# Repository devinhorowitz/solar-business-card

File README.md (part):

# SOLAR-GLOW · DRH

A business card that runs on light. An AVR microcontroller breathes four amber LEDs
*through* the board — a monogram cut into the front copper that glows when the rear LEDs
backlight it through the bare fiberglass — while a pair of indoor solar cells trickle-charge
a supercapacitor bank that holds the charge.

<sub>The assembled card — Ti back-shell, resin diffuser brace, 0.60 mm PCB and eight M2 brass screws.
Not an artist's impression: every surface is the committed STEP-derived STL, the outline and the
eight mount positions come straight out of the `.kicad_pcb`, the Z stack is the one
`enclosure/fit_rules.py` enforces, and the show face is the **raytraced board itself** — the
monogram window, the ENIG, the contactless mark and the contact line are the real artwork, not a stand-in.
Re-route the front and this picture follows. Stills, the exploded and reverse views, and the full
respin are in [`enclosure/README.md`](enclosure/README.md).</sub>

> **Status: v4.0 (managed-solar redesign) in progress** -- working files are `v4_0`, currently the v3.0
> baseline being reworked to the AEM10300 active-harvest architecture (see the design-notes v4 addendum +
> `v4-aem10300-prewiring.md`). **v3.0 -- fully routed, audit-clean, not yet fabbed -- is frozen as the final
> unmanaged-solar revision.**
> Two-layer, 0.6 mm FR4, bound for PCBWay; the 4-layer **v2.3** is the fallback design, kept in git history (not the working tree).
> The one thing standing between here and a build is the **energy budget** — harvest vs. draw under
> real indoor light has never been measured. See *“The open question.”*

### Current revision — the one canonical summary

| What | Current | Notes / fallback |
|---|---|---|
| **PCB** | **v4.0 - 2-layer** (F / B) | GND = full-board B.Cu pour; VS = routed B mesh. **v2.3 (4-layer: F / In1 GND / In2 VS / B) is the fallback design, in git history.** v2.1 was 6-layer (history). |
| Board | 50.80 × 88.90 mm, r3.0 corners, **0.60 mm** FR4, ENIG, matte-black mask | 0.6 mm — committed in the board stackup (frees the shell floor to 1.0 mm) |
| Mounting holes | **8× M2, GND** -- 4 corner (MH1-4) at **(2.87, 2.87) / (47.93, 2.87) / (2.87, 86.03) / (47.93, 86.03)** (pitch **45.06 × 83.16 mm**) + 4 panel-corner (MP1-4) at **(2.87, 28.63) / (47.93, 28.63) / (2.87, 60.27) / (47.93, 60.27)** | corners concentric with the r3.0 fillets; MP1-4 at the E/W mid-edges for the shell clamp |
| **Enclosure** | **Ti back-shell** - 1.00 floor, 1.80 cavity, overall **3.55 mm**; center support via the single-piece resin diffuser brace. **Respun 2026-07-29 against the real board** — the brace had 593 mm³ of resin inside three supercaps and the shell lip sat on 4.17 mm² of live pad; both geometries are now computed from the board and gated by `check_consistency` **[8]**. | 8-hole pattern (4 corner + 4 panel-corner); see [`enclosure/README.md`](enclosure/README.md) |
| BOM | **generated from the design** — there is no hand-authored master; most passives 0402 with the precision/bulk set on **0603** (C4/C13/C25/C22/C23/R5/R6/R15/R16) and **0805** (C26/C27); **SJ1 removed outright 2026-07-30** (lineage row only); Q2 + R18 added by the cold-start-deadlock fix | line items come from `scripts/bom_split.py` (schematic + the board's own `exclude_from_bom`/`dnp` flags); the buy documents are written into `Generated/fabdocs/` every CI run; live availability + pricing in `BOM/README.md` (`python3 BOM/check_stock.py`). Both `*-BOM.xlsx` masters were culled 2026-08-02 and live in git history |
| Firmware | AVR64EA28 C, register-verified **and compile-verified in CI**; not yet on hardware | LED pin map re-mapped in v3.0 (see `firmware/README.md`) |

*How thin 3.55 mm is, in things a hand already knows — thinner than three stacked pennies, almost exactly a ten-card stack of standard business cards, 41% of an iPhone 17 Pro. True relative scale; the card's number is measured from the committed back-shell STL by `scripts/ref_figures.py`, so the figure follows the artifact.*

### Where the truth lives — how these docs stay from drifting

Each fact has exactly one home; everything else points at it rather than restating it.

| Domain | Source of truth |
|---|---|
| Board copper / geometry / holes | `PCB/solar-glow-drh-v4_0.kicad_pcb` + `.kicad_sch` |
| Back-shell medallion (ring text, monogram, serial №) | `enclosure/medallion.py` — the shell generator and its drawing both import it; bump `SERIAL` there and CI regenerates the STEP/STL/drawing (a kibot trigger since 2026-07-31) |
| Fabrication panel (PCBWay) | `scripts/panelize.py` — derived from the board on every CI run into `Generated/panel/`; never hand-maintained |
| README renders | `scripts/render.py` — raytraced from the board/panel on every CI run into `Generated/docs/`; add a target there rather than committing a hand-made image |
| Enclosure **fit rules** | `enclosure/fit_rules.py` — one home for the brace footprint, the lip bands and the boss scallops; both generators import it and check [8] asserts it. That proves the RULES; whether the emitted solids carry them is `scripts/assembly_drc.py`, which slices the STLs (2026-11-12 — a rule one generator never applied passed check [8] for three months) |
| Enclosure part positions | `enclosure/board_parts.py` — true body ∪ pads, read from the committed `.kicad_pcb` |
| Enclosure geometry | `enclosure/solar-glow-drh-v4_0-backshell-0p6b-brace-cad.py` (prints the Z-stack; regenerates the STEP) |
| Assembly views | `enclosure/assembly_render.py` — regenerated from the STLs + the board; not hand-made |
| Firmware pin map + knobs | `firmware/board.h` (+ `firmware/README.md`; both match the schematic) |
| BOM | **the design itself** — `scripts/bom_split.py` derives every line from the schematic plus the board's `exclude_from_bom`/`dnp` flags, and writes the two buy documents into `Generated/fabdocs/` on each CI run. `BOM/README.md` is **derived too**: a live stock/lifecycle/price table regenerated by `BOM/check_stock.py` (needs distributor API keys, so manual-apply like the mask art). _(There is no spreadsheet master; both `*-BOM.xlsx` files were culled 2026-08-02 — git history only.)_ |
| Design *reasoning* / lineage | `solar-glow-drh-design-notes.md` |
| Open work / cross-domain to-dos | `TODO.md` (an index of what's left; each item points back at the files above) |

When a number here disagrees with a source-of-truth file, the source file wins and this table is the
thing to correct. The `solar-glow-drh-v2-*` docs are v2-era history (banner-marked at the top of
each); read them for lineage, not for current values.

---

## What it is

A business-card-sized PCB — **50.8 × 88.9 mm, 0.6 mm FR4, ENIG, rounded corners** — that:

- **Harvests** indoor light with **two** ANYSOLAR solar cells merged into a single solar node (SRC) that feeds the AEM10300 harvester (U8),
  which runs the MPPT and handles reverse-blocking so neither panel back-feeds the
  other - the v3 per-panel blocking diodes are removed.
- **Stores** energy in **four** series-parallel supercapacitors -- a **hybrid tank** (two larger
  SS17 cells + two WS17), **1.40 F at 5.5 V** — two EQUAL 2.8 F stages (SC1∥SC2 above MID, SC3∥SC4
  below), **≈ 21 J nameplate but 15.1 J stored and 9.8 J spendable** once the AEM's strapped 4.65 V
  `VOVCH` ceiling and the 2.75 V glow floor are applied — with the AEM10300 harvester (U8) balancing
  the series midpoint (MID) against leakage mismatch between those two identical stages; the safe 3.3 V VS rail
  is set by the U9 TPS7A0233 LDO, not a shunt clamp.
- **Glows** by back-lighting a **“DRH” monogram** that’s cut into the front copper: a gold
  ENIG field with the three letters opened to bare FR4. Four reverse-mounted amber LEDs on the
  back fire up through the translucent substrate, so the letters themselves light up — and PWM
  on the LED drives makes them breathe.
- **Wakes** to a **tap.** A 3-axis accelerometer feels you pick the card up (or the enclosure
  being tapped) and interrupts the MCU out of sleep — no button, no moving parts.

The front face stays naked — solar cells and the glowing monogram exposed — and the dense work
all lives on the back, ready for an optional machined-metal back-shell.

> **A note on lineage:** earlier revisions (REV J and before) were *generated from Python* —
> geometry and Gerbers emitted by script, no layout tool in the loop. **v2.1 is a full KiCad
> design** (schematic + board), continued through v4.0. The old generators are kept only as
> history; the KiCad files are the source of truth.

---

## How it works

| Block | Part | Notes |
|---|---|---|
| MCU | **AVR64EA28** (28-VQFN) | TCA0 hardware PWM, I²C to the accel, charge/sleep logic; 2026-07 family swap from the AVR64DD28 (12-bit diff ADC + PGA; no MVIO on the EA, so the DD-era SJ1 strap was deleted outright, 2026-07-30) |
| Solar | **2× ANYSOLAR SM141K06TF** | monocrystalline indoor cells (Voc 4.15 V), in parallel — two panels ≈ 2× the harvest |
| Harvest PMIC | **e-peas AEM10300** (U8, QFN-28 4×4) | MPPT buck-boost that merges both panels at SRC and charges the supercap tank (STO) - replaces the v3 per-panel blocking diodes |
| Storage | **2× SCHURTER 3-153-440** (SS17, 1.8 F) + **2× 3-153-438** (WS17, 1.0 F) | hybrid tank, 2.75 V/cell, wired 2S2P as **two EQUAL 2.8 F stages** (SC1∥SC2 `STO`→`MID`, SC3∥SC4 `MID`→`GND`) → **1.40 F @ 5.5 V**; ≈ 21 J nameplate, **15.1 J stored** at the AEM's strapped 4.65 V ceiling, **9.8 J spendable** above the 2.75 V glow floor. AEM holds MID against *leakage* mismatch between the two identical stages — not a capacitance imbalance; there isn't one |
| Midpoint balance | **AEM10300 (U8) BAL** | the harvester balances the 2S supercap midpoint (MID net) - replaces the v3 ALD910025 dual SAB MOSFET |
| Rail regulator | **TI TPS7A0233PDQNR** (U9, X2SON-4 since 2026-08-05) | nanopower LDO (~25 nA Iq) regulates STO down to the fixed **3.3 V VS rail** the MCU + accel run on - replaces the v3 TLV3011 + PNP shunt clamp |
| LEDs | **4× ams OSRAM LA P47F** (amber) | reverse-mount; glow through the FR4 window, **150 Ω** ballast each |
| LED master switch | **SW2** (solder-bridge) | OFF / ON — bridged feeds `ANODE` straight from `STO`, open is a true hardware off _(the TINY dim position and its R12 shared ballast were deleted 2026-08-05; PWM duty owns dimming)_ |
| Motion | **ADI ADXL367** | 3-axis accel; tap / double-tap wakes the MCU via interrupts; 0.89 µA (swapped from LIS2DH12 on backorder) |
| Light sense | **R5 / R6 divider → PD2** | SRC ÷ 2 off the *merged solar input* (not the rail) - tracks light directly; doubles as wake-on-light |
| NFC | **NXP NT3H2211** (NTAG I²C plus 2K) | present from v3.0 - a contact **vCard** a phone taps to save; field-detect (FD, PA6) also wakes the glow - I²C `0x55`, shares the accel's bus; VCC **power-gated by `U6`** (`NFC_EN`/PA7, off by default); the **U7 MB85RC512TY FRAM** (I²C 0x50, C28) rides always-on VS parked in its 0.2 µA I²C Sleep mode (the 2026-07-23 back-power fix - see design notes) |

**Breakouts and features:** a **TC2030** Tag-Connect pad (`TC1`) for hands-free UPDI
programming, a backup UPDI header (`J1`), a **5-pad bench strip** on the back east edge
(`TP1` SRC + `JP1` GND/STO/SCL/SDA - bare SMD probe pads for bench power injection and an I²C
tap; pinout in `solar-glow-drh-v2-hardware.md`), and **eight grounded M2 mounting holes** (four corners + four panel-corner at the E/W mid-edges). (The `SB1–4`
bridges — per-LED **force-on**, not "disable" as this line long said — were deleted with TINY mode on 2026-08-05. The DD-era
VDDIO2 tie jumper `SJ1` is gone — DNP'd at the AVR-EA swap, deleted from the schematic and board outright on 2026-07-30. The v2-era
`JP1`/`JP2` 2.54 mm breakout headers are gone; the `JP1` name is reused for the strip.)

Full part numbers, pricing, and per-part datasheet links are in
**[`BOM/README.md`](BOM/README.md)** - the live availability table (generated; there is no spreadsheet
master, both `*-BOM.xlsx` files were culled 2026-08-02 into git history): every orderable line carries a
live-verified distributor P/N, stock and price, re-checked by `BOM/check_stock.py` rather than typed. **U6 is moving to
TPS22916CYFPR** (DSBGA-4 YFP, 0.5 mm max — the 2026-08-06 ultrathin swap; schematic done, board sync pending — see
`PCB/README.md`'s BOM table. It succeeds the TPS22919 SC-70 that landed 2026-08-05 — itself the leakage upgrade over
the `TPS22917DBVT` — trading +8 nA typical OFF-state leakage for 0.6 mm of height and a 16× better ON-state IQ,
so every component clears 1.1 mm for the ultrathin-card option) with **R14 (1 M `NFC_EN` pulldown)**; the stale
JP1/JP2 rows are dropped (the `JP1` designator is reused in v3.0 for the bench pad strip - bare pads,
no BOM part). Passives are X7R / AEC-Q200 / precision grade: most on **0402** lands, with the
stability upsizes on 0603 (C22/C23, R5/R6, R15/R16, plus the bulk caps C4/C13/C25) and 0805
(C26/C27, and C9's NFC tank cap — fitted 47 pF, derived not trimmed). SJ1 is culled. Lineage: v2.2 added the NFC parts (U5 / C8 / C9 / R13); the `v2 2` and older
BOM files stay in the repo as history.

---

## The board

- **Two copper layers** on 0.6 mm FR4 (v3.0): **F.Cu** signal/parts and **B.Cu**. **GND is a
  full-board B.Cu pour** (`GND_B` zone) with stitch straps, and **VS is a routed mesh on B** — the
  4→2-layer conversion of v2.3, whose internal GND/VS *planes* moved onto the back copper. The
  4-layer **v2.3** (F · In1 GND · In2 VS · B) is the fallback (recoverable from git history) if the
  back-side trace texture showing faintly on the naked front reads wrong.
- **The glow window is a keepout on every layer.** The monogram cutout and the four LED
  light-paths are voided through both layers so nothing — copper pour, trace, or via —
  shadows the light between the rear LEDs and the front face. The rear soldermask is left
  *open* over the window on purpose: bare ENIG reflects the LEDs’ light forward instead of
  absorbing it.
- **Rail discipline.** The supercap stack can sit near 5.5 V, but the accelerometer tops out at
  3.6 V - so the **U9 TPS7A0233 LDO** regulates the supercap tank (STO) down to the fixed
  **3.3 V VS rail**, directly bounding what the accelerometer sees. Its ~25 nA quiescent
  draw is negligible against the other always-on loads, and it regulates VS itself rather
  than the solar input. (v3's TLV3011 + PNP shunt clamp and the per-panel blocking diodes
  are gone - the AEM10300 now owns the harvest path.)
- **Power planes** carry the supercap charge/discharge currents; the four cells eat the better
  part of the back, so the layout is geometry-bound and the planes earn their layers.

---

## The open question — read this before building a batch

The board is well-verified; the **energy budget is not.** A solar cell’s headline rating is a
full-sun number, and indoor light delivers a small fraction of it, while four breathing LEDs
average several milliamps. The two-panel harvest and the tank — **9.8 J spendable**, not the 21 J
nameplate — are sized to **harvest
slowly and glow in bursts** — but that bet has never been put on a meter.

What changed the math since the early notes: the LED string is fed from the **STO supercap tank** (through the
SW2 anode switch), which the AEM10300 holds at up to **4.65 V** (VOVCH), and the ballasts are **150 Ω** -- so each
LED peaks near **~16 mA** at a full tank ((4.65 V - amber Vf ≈ 2.25 V)/150 Ω, the figure `firmware/README.md`
quotes), sagging toward zero as STO discharges. (VS, the regulated 3.3 V LDO output, powers the MCU and accel,
not the LEDs.) Four on at once is a real load against an indoor harvest measured in fractions of a milliamp.

**First move when boards arrive:** put the cells under your actual target lighting and measure
**harvest current against LED draw** before you populate a full stack. That single number sizes
the duty cycle, the feature set, and whether the always-on accelerometer earns its microamps.

---

## Repository layout

```
solar-business-card/
├── README.md                       # this file (canonical current-revision summary)
├── PCB/                            # KiCad projects
│   ├── solar-glow-drh-v4_0.kicad_pcb   # the board: v4.0 managed-solar rework (AEM10300), 2-layer (source of truth)
│   ├── solar-glow-drh-v4_0.kicad_sch   # schematic: synced to the v4.0 board netlist
│   └── README.md                       # order & build guide
├── BOM/                            # bill of materials (moved from PCB/ 2026-08-01)
│   ├── README.md                       # GENERATED live availability/price table (check_stock.py)
│   ├── check_stock.py                  # live DigiKey/Mouser availability check -> README.md
│   └── README.md                       # DERIVED: stock/lifecycle/price table with red-X dead lines (regenerate, don't edit)
├── solar-glow-drh-design-notes.md  # design rationale, energy model, lineage (incl. the v3.0 chapter) — the one prose file that stays at root, beside this README
├── docs/                           # project notes & records (moved from root 2026-08-01) + the LED sweep tuner
│   ├── solar-glow-drh-v2-hardware.md    # as-built wiring & pin map (v2-era lineage; banner at top)
│   ├── solar-glow-drh-v2-mechanical.md  # board mechanics, keepouts, access (v2-era lineage; banner at top)
│   ├── v4-aem10300-prewiring.md         # the v4 net/pin plan — applied 2026-07-30, kept as the record
│   ├── v4-schematic-sync-checklist.md   # the sch→board sync procedure — DONE, kept as the record
│   ├── harvest-bench-fixture-handoff.md # the energy-budget bench fixture (the #1 open gate's rig)
│   ├── harvest-budget-test-board.md     # the harvest test-board concept
│   ├── eink-display-variant-notes.md    # e-ink variant study (concept, not adopted)
│   ├── firmware-to-pcb-open-items.md    # v3-era cross-team memo (SUPERSEDED; record only)
│   ├── mcp-setup.md                     # sourcing MCP servers setup (DigiKey/Mouser)
│   ├── kicad-happy.md                   # the external second-opinion analyzer: pinned run recipe + the 2026-08-01 baseline triage
│   ├── thomsonlint.md                   # the ontology-guided second reviewer: pinned run recipe + the 2026-08-01 review record
│   └── led-sweep-tuner.html             # interactive LED-constant sandbox (firmware/README links it)
├── firmware/                       # bare-metal C (AVR64EA28); compile-verified, see firmware/README.md
├── bench/                          # pogo-plate bench monitor: Pico firmware + host dashboard (see bench/monitor)
├── datasheets/                     # fitted parts + documented substitutes, named "REF  MPN  $price.pdf"
│                                   #   (survey sheets and replaced-part docs culled 2026-08-01 — git history)
├── enclosure/                      # Ti back-shell + resin brace: CAD / STEP / STL / drawings / assembly views
│                                   #   fit_rules.py + board_parts.py = the geometry both generators derive from
└── (v0-prototype/ and enclosure/engraving-studies/ culled 2026-08-02 — concluded history, kept in git history; the medallion the studies produced ships in enclosure/medallion.py)
```

---

## Building the board

The board is a KiCad project — open it, run DRC, and export the fab set:

1. Open `solar-glow-drh-v4_0.kicad_pro` in **KiCad** (2026 file format).
2. **Run DRC.** It comes back clean apart from the intentional exceptions catalogued in
   `PCB/README.md` and `solar-glow-drh-design-notes.md` (the NFC coil `LA`↔`LB` short, the eight
   GND-tie mounting-hole/gold-frame contacts, the two plating-bus stubs crossing Edge.Cuts at
   x=25.4, the illumination copper inside the glow window, and the benign `lib_footprint_issues`
   plus the **intentional** `BTN` global label on PA5 — the documented future-button pin
   (a deliberate no-fit; recipe in `firmware/README.md`), not a loose end). Fill zones (press **B**) before checking.
3. **Plot Gerbers + drill** from KiCad's own Fabrication Outputs and order from **PCBWay**
   (**2-layer**, 0.6 mm; selective hard gold + plating bus + resin-fill/cap per `PCB/README.md`).

> The supercap land is the one thing to never get wrong. **Both** SCPC cells — the 39 mm
> **SS17** (SC1/SC3) and the 28.5 mm **WS17** (SC2/SC4) — solder to **flat pads under the body**
> (the asymmetric P/N widths are the polarity key), **not** to the folded end tabs, which are
> non-solderable mechanical locators. The footprints here are built to the correct under-body
> land; don't substitute an end-tab land.
>
> Mind the two lengths. Assuming every cell was the 28.5 mm WS17 is exactly what put 593 mm³ of
> brace inside SC1 and SC3 — see [`enclosure/README.md`](enclosure/README.md).

---

## Assembly order (when boards arrive)

1. **Validate the energy budget first** — harvest vs. LED draw under real lighting (above).
2. **Reflow the SMD parts** — the QFN MCU and the LGA accelerometer need hot air / a hotplate;
   the EP and the accel pad reflow to their planes.
3. **Flash firmware** over UPDI — the Tag-Connect pad (`TC1`) is the no-header path; `J1` is the
   backup header. **This step moved ahead of the cells on 2026-07-30**, when TC1 was deliberately
   moved to `F.Cu`: PV1's body covers the pad cluster, so a pogo cable cannot reach it once the
   cell is on. The trade is a good one — the old position was under `SC1`, which is *reflowed*, so
   the window used to close before the board was even finished. See the warning box in
   [`PCB/README.md`](PCB/README.md).
4. **Hand-solder last** — the solar cells (heat-sensitive: ≤ 260 °C / 2 s, no IPA), and set the
   **SW2** bridge: bridged = ON, open = OFF.

---

## Firmware

A first implementation now lives in **`firmware/`** — bare-metal C, **verified at the register
level** against the AVR64EA28 and ADXL367 datasheets and **compile-verified in CI** (warning-free
against the AVR-Ex DFP; not yet run on hardware). Its knobs, wake model, and power notes are in
**`firmware/README.md`** (authoritative); the wiring it targets is **`firmware/board.h`**, which
`check_consistency` **[1]** holds against the schematic netlist pin by pin. (The complete v2-era
pin map in **`solar-glow-drh-v2-hardware.md`** is lineage, not a current source — see the truth
table above.) Final
duty-cycle and feature tuning stay **gated on the energy-budget measurement** below. In short,
the board gives it:

- **LED breathing** — the four LEDs sink into **PA0–PA3 = TCA0 WO0–WO3**, so split-mode PWM
  drives all four as independent 8-bit channels (the 150 Ω ballast sets the peak; PWM sets the
  average, so you trim brightness *below* that ceiling).
- **Tap-to-wake** — the accelerometer’s two interrupts land on **PF1 / PF0**; configure
  tap / double-tap and let it pull the MCU out of sleep.
- **NFC contact tag** — `U5` (NXP NT3H2211, on the board from v3.0) carries a **vCard** a phone reads on a
  tap to save the contact (RF-powered, so it reads with the cap flat), and its **field-detect**
  line wakes the same glow. The tag has no sleep state and would draw **~195 µA** continuously — the
  card's largest idle load — so firmware **power-gates** its VCC through a load switch (`U6`) on
  **NFC_EN (PA7)**, held **off by default** and raised only around an I²C access; the vCard read and
  the FD-wake both run on the phone's field power, so they still work with the tag's VCC off. Shares
  the I²C bus with the accel (`0x55` vs `0x1D`). See `firmware/README.md` → *NFC contact card*.
- **Light sensing** - the divider taps the **merged solar node SRC** (SRC ÷ 2) into **PD2** (AIN2), so it
  reads light directly — ~0 V dark, rising under light; firmware adapts the glow to available
  light and can also read **VDD/10** and the internal temp sensor.
- **Wake-on-light** — the card can also wake when light appears, with no tap. The implemented
  path is an **RTC-timed ADC poll** in deep Power-Down (sample PD2/AIN2 every ~1–2 s, glow on a
  dark→light rise). The tempting *instant* AC0-comparator version was checked against the
  datasheet and found **non-viable on this part** — the AC interrupt doesn't update with the
  peripheral clock stopped, and the AC isn't a Standby/Power-Down wake source, so it would never
  fire. Instant response isn't lost: the accelerometer interrupt wakes from Power-Down, and
  picking the card up to carry it into the light *is* that motion. (Standing current: **≥ ~2.7 µA — a
  2.0 V-referenced lower bound, not a measurement** (the 2026-08-01 pressure test found the NFC tag's
  FD-pin leakage, 1.5 µA typ / 10 µA max, unbudgeted in that sum) — the always-on accelerometer
  (ADXL367, 0.89 µA typ *at 2.0 V*) no longer dominates it, and neither the poll nor the NFC tag do,
  the latter being power-gated off by default — see `firmware/README.md` "Power notes" for the honest
  ledger and the bench item.)
- **Low-power housekeeping** — `VREGCTRL.PMODE = AUTO` for sub-µA power-down; RTC/PIT off the
  internal ULP oscillator (no crystal); an EEPROM “times-activated” counter that survives a
  full supercap drain; and the core **IDLE-sleeps through the breathing glow** while TCA0 keeps
  the PWM running, rather than busy-waiting. (An autonomous CCL + EVSYS light-wake is a possible
  v-next, but isn't what the current firmware does.)

Still open (what the bench measurement unlocks): final breathing-curve and tap-gesture tuning,
charge / brown-out management around the supercap bank, and the duty-cycle adaptation the
harvest number sizes.

---

## Enclosure

A back-only **machined-titanium** shell hugs the populated rear; the front stays naked. A
single-piece **resin diffuser brace** fills the cavity, carries centre support, backs the
monogram window and holds the ferrite over the NFC coil. CAD, STEP, STL, fab notes and
dimensioned drawings are in `enclosure/` — full detail in
[`enclosure/README.md`](enclosure/README.md).

**Respun 2026-07-29 against the real board, because neither part would have assembled.** The
brace's middle band was sized for supercap bays ending at y31.15 / y57.75 — the 28.5 mm WS17
length — while SC1/SC3 are 39 mm SS17 cells, so it put **593 mm³ of solid resin inside three
1.70 mm cans**. The shell's support lip landed on nine B-side parts including **4.17 mm² of
live pad** (`STO`, `STO_LDO`, `VS`, `NFC_EN`) under grounded titanium — fitting it shorted the
storage rail — and five of the eight M2 bosses fouled a part, two on live nets.

Both geometries are now **computed from the board** (`enclosure/fit_rules.py`, reading part
positions from `enclosure/board_parts.py`) rather than hand-placed, and gated by
`check_consistency` **[8]**. Interference is structurally impossible: a part the brace cannot
span is *subtracted* from its footprint rather than pocketed. No board change was required.

The decisions that matter once it's cut: **titanium (Ti-6Al-4V Grade 5)**, **3-axis CNC-milled**
by PCBWay, **bead-blast** finish. The cavity is **cap-limited to 1.80 mm** by the four 1.70 mm
supercaps; the floor is a **true uniform 1.00 mm** (the old 0.05 mm U7 relief pocket was deleted
2026-07-28 — U7 is the 0.90 mm DFN-8, not the 1.75 mm SOIC it was sized for); overall height
**3.55 mm**. **Eight** bosses on the v4 8-hole pattern (four corner, concentric with the r3.0
fillets, plus four panel-corner), each **scalloped** clear of whatever fouls it — a supercap by
that can's own bay clearance, since its body tolerance lands on the edge the boss faces — while
keeping ≥ 80.3 % of its M2 thread annulus. Retention is **eight M2×3 slotted brass screws**, not a press
fit; the head is Ø3.0 and the tip lands **flush** in a Ø3.0 back spotface.

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
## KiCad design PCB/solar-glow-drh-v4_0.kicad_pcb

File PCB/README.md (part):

# SOLAR-GLOW · DRH - PCB (v4.0): Order & Build Guide

<table>
<tr>
<td width="50%"></td>
<td width="50%"></td>
</tr>
<tr>
<td align="center"><b>Front</b> — the card face</td>
<td align="center"><b>Back</b> — the component side</td>
</tr>
</table>

**This is what PCBWay ships**: the 1-up card still attached to its 65.6 × 103.7 mm frame, before
you snap the two tabs. The gold ring inset in the frame is the hard-gold plating bus, mask-opened
so the plating rack has bare copper to clip, with a spur crossing each break tab into the card at
x = 25.4. Both faces are raytraced from the panel CI actually generates — see
`scripts/render.py`, and "The PCBWay panel" below. No components are shown because none are
fitted at this stage; that is the fab's deliverable, not an omission.

## Assembled

<table>
<tr>
<td width="50%"></td>
<td width="50%"></td>
</tr>
<tr>
<td align="center"><b>Back</b> — 53 fitted parts</td>
<td align="center"><b>Front</b> — the two solar cells</td>
</tr>
</table>

The same board with its components on: 52 of the 73 footprints carry a 3D body, which is every part
that actually gets populated (recounted 2026-08-05 after SB1–4 and R12 left with TINY mode; the
2026-08-01 count was "53 of 78"). The other 21 are the drill/mount set (MH1–4, MP1–4, `NPTH_mech`),
the SW2 solder bridge, the bare programming and probe lands (TC1, `TC1/b`, TP1–TP7, JP1),
and **J1**, which is DNP.

> **Read the big grey slabs as ENVELOPES, not as photographs.** The four supercaps, the two solar
> cells, the LEDs, both QFNs, the FRAM, the accelerometer and the NFC tag are **clearance solids**
> generated by `scripts/make_3d_models.py` — each is its part's maximum outline at its **maximum**
> height, because the question they exist to answer is "does the brace clear it?" and a pretty model
> at the wrong height would be worse than useless. They are not appearance references. The chip
> passives and SOT-23s are stock KiCad models and do look roughly like the real parts.
>
> The supercap **locator tabs are deliberately absent** — see `TODO.md`; their real folded geometry
> has never been measured, so the envelope near the two short edges is unverified.
>
> **Every body you see is rendered from this repo, not from a KiCad install.** The nine stock models
> live in `PCB/kicad-3dmodels/` because the image CI renders in carries no 3D library at all — that
> was measured, not assumed (`models: 15/53 resolve ... NO stock 3D library found`), and it is why an
> earlier version of this render was missing every chip passive and both SOT-23s. `render.py` points
> `${KICAD10_3DMODEL_DIR}` at the vendored copy when the host has none, and consistency check [5]
> fails if a new part references a stock model nobody vendored.

---

This folder holds the **board** for SOLAR-GLOW · DRH — the KiCad project, the bill of
materials, and the artwork reference for the SW2 selector. It is the thing you fab and
populate. This README is the procedure: **how to order the bare PCB, how to order the
parts, and how to build the assembly.**

> **One revision lives here.** As of 2026-07-28 that is **v4.0**; the seven `*-v3_0.*` files
> (board, schematic, project, prl, dru, and both BOMs) were removed, the same way v2_1–v2_3 were
> before them. Superseded revisions are kept by git, not by this folder — carrying a second 1.6 MB
> board around only invites someone to open the wrong one. To get one back:
> ```sh
> git log --diff-filter=D -- PCB/solar-glow-drh-v3_0.kicad_pcb   # the commit that removed it
> git show <sha>^:PCB/solar-glow-drh-v3_0.kicad_pcb > /tmp/v3.kicad_pcb
> ```
> **`enclosure/solar-glow-drh-v4_0-backshell-*` is unaffected.** Those files are current and
> fab-ready. _(They carried `v3_0` names until 2026-08-19 — the revision the shell was first cut
> against — and this note used to explain why that was fine. It stopped being fine when the
> DRAWING generator was found stamping **`REV v3.0`** into the title block of the sheet a
> machinist cuts to; a stale revision on a fab document is not a naming preference. Renamed and
> re-stamped to v4.0 in one commit. The v4 board carries the identical 8-hole pattern, so the
> geometry never moved.)_

```
PCB/
├── solar-glow-drh-v4_0.kicad_pro     # KiCad project (open this)
├── solar-glow-drh-v4_0.kicad_sch     # schematic
├── solar-glow-drh-v4_0.kicad_pcb     # board — 2-layer, routed, teardropped (source of truth)
├── solar-glow-drh-v4_0.kicad_prl     # local project state — versioned DELIBERATELY (the GUI layer setup travels with the project; unlike Generated/'s prl side-effect, which was culled 2026-08-01)
├── solar-glow-drh-v4_0.kicad_dru     # two-tier design rules (PCBWay floor + marginal band)
├── solar-glow-drh.kibot.yaml         # CI recipe — regenerates ../Generated/ on every push
│                                     # (the BOM masters moved to ../BOM/ on 2026-08-01, beside the live
│                                     #   stock checker; the tree line here that called the assembly xlsx
│                                     #   "stale at its 36-row era" was itself stale — the file was rebuilt
│                                     #   2026-07-30 at the 47-part placed set, see ../BOM/)
├── kicad-3dmodels/                   # the 9 stock KiCad .step bodies this board uses, mirroring the
│                                     #   library layout (CC-BY-SA 4.0, licence bundled). CI's render
│                                     #   image ships NO 3D library, so without these the assembled
│                                     #   render silently loses 38 of 53 component bodies.
└── DRC.rpt                           # last GUI DRC export (user-refreshed at board edits; CI keeps the live
                                      #   reports in ../Generated/. ERC.rpt was culled 2026-08-01 — its 07-27
                                      #   export had outlived two schematic generations; read Generated/…-erc.html)
                                      # (v2_1 / v2_2 / v2_3 / v3_0 revisions live in git history, not this folder)
```

> **The board is the source of truth.** `solar-glow-drh-v4_0.kicad_pcb` / `.kicad_sch`
> govern. The design *reasoning* lives one level up:
> - `../firmware/board.h` + `../firmware/README.md` - as-built pin map and net list (the firmware target); `../docs/solar-glow-drh-v2-hardware.md` is frozen v2 lineage only.
> - `../docs/solar-glow-drh-v2-mechanical.md` — board envelope, heights, mount holes, keepouts.
> - `../solar-glow-drh-design-notes.md` — why each decision was made; the landmines.
> - `../README.md` — the project overview and the standing open question (energy budget).
>
> Where a number here and a number in those files ever disagree, re-read the `.kicad_pcb`.

> **Read this before committing money: the energy budget has never been measured.** Harvest
> under real indoor light versus four breathing LEDs at the current 150 Ω ballast is an
> unproven bet. It does not stop you fabbing one board — it stops you populating a *batch*.
> See **First power & bring-up** below and `../solar-glow-drh-design-notes.md` §2.

---

## Board at a glance

| Parameter | Value |
|---|---|
| Outline | 50.80 × 88.90 mm rounded rectangle, **3.0 mm corner radius** |
| Layers | **2 copper**: F.Cu (cells, plating ties, monogram art) · B.Cu (everything else) |
| Power architecture | **GND = full-board B.Cu pour** (~3000 mm²); **VS = routed B.Cu mesh** |
| Finished thickness | **0.6 mm** FR4 |
| Surface finish | **ENIG** + **selective hard (electrolytic) gold** on the F.Cu gold set — the plating bus exists to feed it (see the order special request; the area itself is drawn on `User.1` by `scripts/mask_art.py` and plots into both fab sets) |
| Soldermask | **Matte black**, both sides |
| Silkscreen | White (back-side identifiers / logos); front face is intentionally bare |
| Components | **52 on the back**; the front carries only the two solar cells (PV1/PV2) |
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
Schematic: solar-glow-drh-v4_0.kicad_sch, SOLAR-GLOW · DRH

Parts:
C1, C29: 100nF; C1; MPN GRT155R71H104KE01D
C3: 100nF; C3; MPN GRT155R71H104KE01D
C4, C13: 10uF; C_0603_1608Metric; MPN GXT188R61C106KE13D
C5: 100nF; C5; MPN GRT155R71H104KE01D
C6: 100nF; C6; MPN GRT155R71H104KE01D
C8: 100nF; C8; MPN GRT155R71H104KE01D
C9: 47pF; C_0603_1608Metric; MPN QSCP251Q470G1GV001T
C11: 220nF; C11; MPN GCM155R71C224KE02D
C12: 100nF; C12; MPN GRT155R71H104KE01D
C22: 1uF; C_0603_1608Metric; MPN GRT188R71E105KE13D
C23: 2.2uF; C_0603_1608Metric; MPN GRM188Z71E225ME43D
C24: 10nF; C1; MPN GCM155R71H103KA55D
C25: 22uF; C_1206_3216Metric_HS_LP085; MPN CL31A226KOCLNNC
C26, C27: 10uF; C_1206_3216Metric_HS_LP085; MPN GRM319R61E106KA12D
C28: 100nF; C_0402_1005Metric; MPN GRT155R71H104KE01D
C30: DNP-trim; C_0402_1005Metric; not fitted
D2: LA P47F; D2; MPN LA P47F-V2BB-24-3B5A-30-R18-Z
D3: LA P47F; D3; MPN LA P47F-V2BB-24-3B5A-30-R18-Z
D4: LA P47F; D4; MPN LA P47F-V2BB-24-3B5A-30-R18-Z
D5: LA P47F; D5; MPN LA P47F-V2BB-24-3B5A-30-R18-Z
FB1: ferrite; L_0603_1608Metric; MPN BLM18PG221SN1D
J1: UPDI hdr; J1; MPN (unpopulated header); not fitted
JP1: GND STO SCL SDA; JP1; MPN (bare pads - no part); not fitted
L2: 10uH; L_1008_2520Metric; MPN DFE252010F-100M=P2
MH1: M2; MH1; MPN (drill - no part)
MH2: M2; MH2; MPN (drill - no part)
MH3: M2; MH3; MPN (drill - no part)
MH4: M2; MH4; MPN (drill - no part)
PV1: SM141K06TF; PV1; MPN SM141K06TF
PV2: SM141K06TF; PV2; MPN SM141K06TF
Q2: DMG1012T; SOT-523; MPN DMG1012T-7
R5, R6, R15: 2M; R_0603_1608Metric; MPN MCT0603MD2004BP500
R14: 1M; R14; MPN AC0402FR-071ML
R16: 1M; R_0603_1608Metric; MPN MCT0603MD1004BP500
R17, R18: 1M; C1; MPN AC0402FR-071ML
RN1: 150R; R_Array_Convex_4x0402; MPN EXB-28V151JX
RN2: 4.7k; R_Array_Convex_2x0402; MPN EXB-24V472JX
SC1, SC3: SS17 1.8F 2.75V; SCHURTER_SCPC_SS17; MPN 3-153-440
SC2, SC4: WS17 1F 2.75V; SCHURTER_SCPC_WS17; MPN 3-153-438
SW2: LED master; SW2; MPN (PCB bridge - no part); not fitted
TC1, TC1/b1: Tag-Connect; TC1; MPN (no part - pogo footprint); not fitted
TP1: VIN; TP1; MPN (bare pad - no part); not fitted
TP2: VS; TPB; MPN (bare pad - no part); not fitted
TP3: MID; TPB; MPN (bare pad - no part); not fitted
TP4: LX_LOUT; TPB; MPN (bare pad - no part); not fitted
TP5: VINT; TPB; MPN (bare pad - no part); not fitted
TP6: BUFSRC; TPB; MPN (bare pad - no part); not fitted
TP7: STO_LDO; TPB; MPN (bare pad - no part); not fitted
U1: AVR64EA28 (VQFN28); U1; MPN AVR64EA28-E/STX
U3: ADXL367; ADXL367 CC-12-4_ADI; MPN ADXL367BCCZ-RL7
U5: NT3H2211; U5; MPN NT3H2211W0FHKH
U6, U10: TPS22916C; TPS22916_YFP0004; MPN TPS22916CYFPR
U7: MB85RC512TY; U7_DFN8; MPN MB85RC512TYPN-GS-AWEWE1
U8: AEM10300; U8_QFN28; MPN 10AEM10300C0000
U9: TPS7A0233PDQNR; Texas_X2SON-4_1x1mm_P0.65mm; MPN TPS7A0233PDQNR

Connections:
ANODE: C13.1, D2.A, D3.A, D4.A, D5.A, SW2.2
BTN: TC1.4, TC1/b1.4, U1.3 (PA5)
BUFSRC: C25.1, TP6.1 (1_1), U8.4 (BUFSRC)
CHG_DIS_G: Q2.1 (G), R18.1, U1.2 (PA4)
EN_STO_CH: Q2.3 (D), R17.2, U8.12 (EN_STO_CH)
FD: U1.4 (PA6), U5.4 (FD)
GND: C1.2, C3.2, C4.2, C5.2, C6.2, C8.2, C11.2, C12.2, C13.2, C22.2, C23.2, C24.2, C25.2, C26.2, C27.2, C28.2, C29.2, J1.3, JP1.1, MH1.1 (1_1), MH2.1 (1_1), MH3.1 (1_1), MH4.1 (1_1), PV1.N, PV1.Nt, PV2.N, PV2.Nt, Q2.2 (S), R6.2, R14.2, R16.2, R18.2, SC3.N, SC4.N, TC1.3, TC1/b1.3, U1.19 (GND), U1.25 (GND), U1.EP, U3.1 (SCLK), U3.3 (MISO/ASEL), U3.7 (GND), U3.8 (ADC_IN), U3.11 (GND), U5.2 (VSS), U6.B1 (GND), U7.1 (A0), U7.2 (A1), U7.3 (A2), U7.4 (VSS), U7.7 (WP), U8.3 (GND), U8.7 (GND), U8.8 (R_MPP2), U8.11 (R_MPP0), U8.18 (STO_CFG3), U8.19 (EN_HP), U8.21 (EN_STO_FT), U8.22 (T_MPP1), U8.25 (STO_CFG2), U8.27 (GND), U8.EP, U9.2 (GND), U9.5 (GND), U10.B1 (GND); also elsewhere on the board
INT1: U1.20 (PF0), U3.5 (INT1)
INT2: U1.21 (PF1), U3.6 (INT2)
K2: D2.K, RN1.2
K3: D3.K, RN1.1
K4: D4.K, RN1.3
K5: D5.K, RN1.4
LA: C9.1, C30.1, U5.1 (LA)
LB: C9.2, C30.2, U5.8 (LB)
LDRV1: RN1.7, U1.1 (PA3)
LDRV2: RN1.8, U1.28 (PA2)
LDRV3: RN1.6, U1.27 (PA1)
LDRV4: RN1.5, U1.26 (PA0)
LX_LIN: L2.1, U8.5 (LIN)
LX_LOUT: L2.2, TP4.1 (1_1), U8.6 (LOUT)
MID: SC1.N, SC2.N, SC3.P, SC4.P, TP3.1 (1_1), U8.13 (BAL)
NFC_EN: R14.1, U1.5 (PA7), U6.B2 (ON)
PC1: U1.7 (PC1)
SCL: JP1.3, RN2.3, TC1.5, TC1/b1.5, U1.9 (PC3), U3.4 (CS/SCL), U5.3 (SCL), U7.6 (SCL)
SDA: JP1.4, RN2.4, TC1.6, TC1/b1.6, U1.8 (PC2), U3.2 (MOSI/SDA), U5.5 (SDA), U7.5 (SDA)
SNS_EN: U1.6 (PC0), U10.B2 (ON)
SRC: PV1.P, PV1.Pt, PV2.P, PV2.Pt, R5.1, TP1.1 (1_1), U8.2 (SRC), U8.28 (CS_IN)
STO: C27.1, FB1.1, J1.2, JP1.2, SC1.P, SC2.P, SW2.1, TC1.2, TC1/b1.2, U8.14 (STO), U10.A2 (VIN)
STO_LDO: C22.1, FB1.2, TP7.1 (1_1), U9.3 (EN), U9.4 (IN)
STO_SNS: C24.1, R15.2, R16.1, U1.11 (PD1)
STO_SNS_PWR: R15.1, U10.A1 (VOUT)
UPDI: J1.1, TC1.1, TC1/b1.1, U1.23 (PF7/UPDI)
VDDIO2: C3.1, U1.10 (PD0)
VINT: C26.1, R17.1, TP5.1 (1_1), U8.9 (R_MPP1), U8.10 (VINT), U8.20 (T_MPP0), U8.23 (STO_CFG0), U8.24 (STO_CFG1)
VNFC: C8.1, U5.6 (VCC), U6.A1 (VOUT)
VREG: C11.1, U3.9 (VREG_OUT1)
VS: C1.1, C4.1, C6.1, C12.1, C23.1, C28.1, C29.1, RN2.1, RN2.2, TP2.1 (1_1), U1.18 (VDD), U1.24 (VDD), U3.10 (VS), U3.12 (VDDIO), U6.A2 (VIN), U7.8 (VDD), U9.1 (OUT)
VSENSE: C5.1, R5.2, R6.1, U1.12 (PD2)

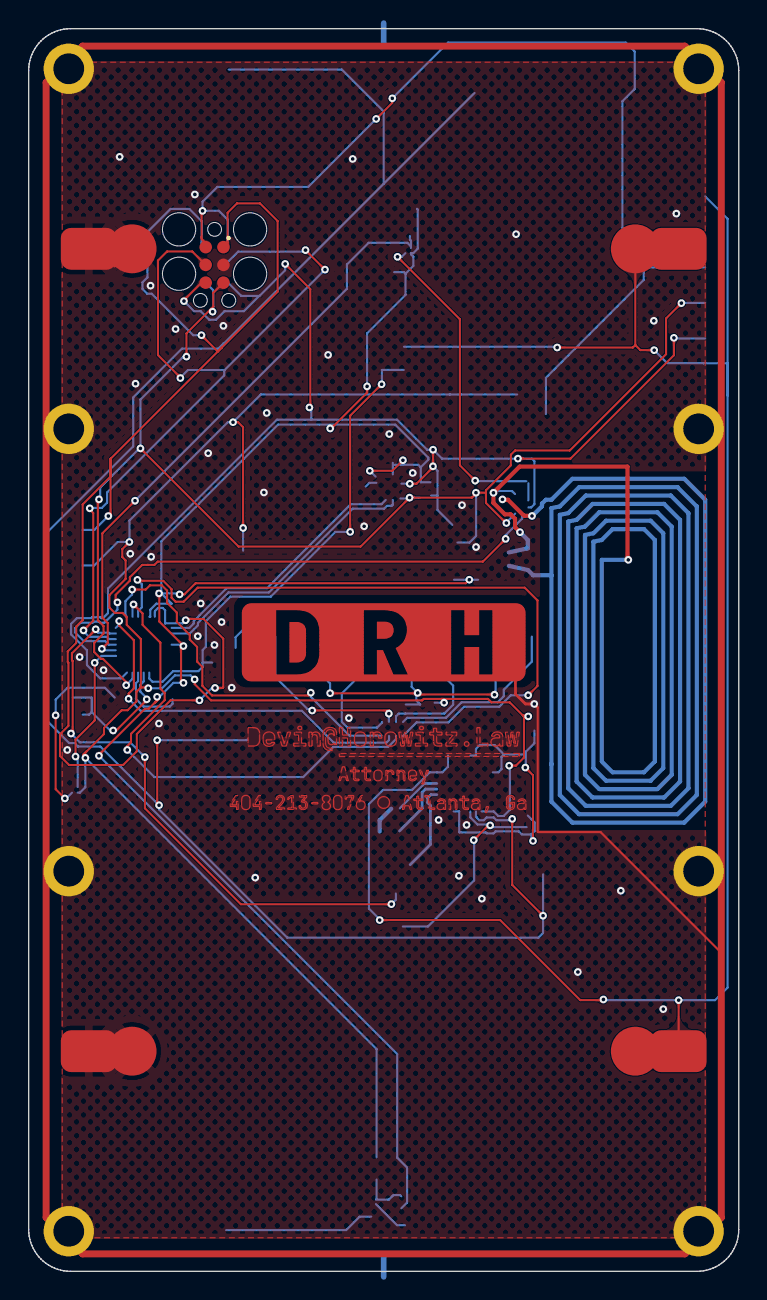
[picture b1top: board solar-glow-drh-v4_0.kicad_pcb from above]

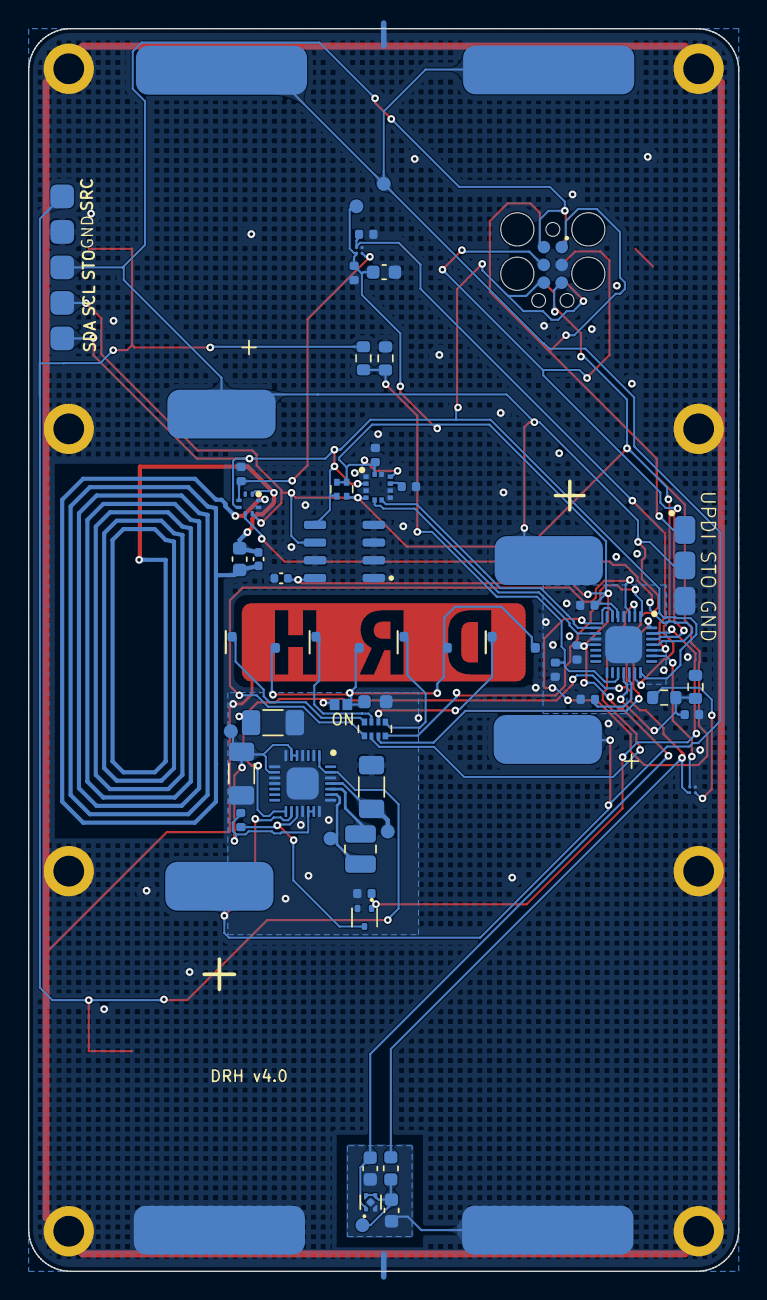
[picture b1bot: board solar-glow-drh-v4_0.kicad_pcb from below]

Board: 2 copper layers, 50.8 x 88.9 mm, 69 parts (58 on the bottom side), 38 nets.

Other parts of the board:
MP1, MP2, MP3, MP4: (no value)

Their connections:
GND: MP1.1 (1_1), MP2.1 (1_1), MP3.1 (1_1), MP4.1 (1_1); also elsewhere on the board

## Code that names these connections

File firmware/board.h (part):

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 *
 * MCU: AVR64EA28, 28-pin VQFN, on the BACK of the board. (v4 family swap from
 * the AVR64DD28: 27/28 pads identical; TWI ALT2, TCA0-on-PORTA, and the
 * PD1/PD2 analog inputs all carry over -- see design-notes 5 addendum.)
 *
 *   pad pinfunc  net      role
 *    26 PA0      LDRV4    LED D5 low-side drive    TCA0 WO0
 *    27 PA1      LDRV3    LED D4                   TCA0 WO1
 *    28 PA2      LDRV2    LED D3                   TCA0 WO2
 *     1 PA3      LDRV1    LED D2                   TCA0 WO3
 *     2 PA4      CHG_DIS_G  Q2 gate: low-side charge-disable buffer (push-pull, HIGH = disable; R18 holds charge ON when MCU dead)
 *     3 PA5      BTN      button pin -- deliberately NO-FIT; a future button = PA5->switch->GND (active-low)
 *     4 PA6      FD       NFC field-detect in (NT3H2211)  FD-wake, both edges; field-powered (works VCC-off)
 *     5 PA7      NFC_EN   NFC VCC load-switch enable (active-HIGH)  output, LOW = NFC off
 *     6 PC0      SNS_EN   STO sense-divider gate (U10 ON, active-HIGH)  output, LOW = divider off
 *     7 PC1      PC1      spare GPIO  -- deliberately unrouted, no breakout
 *     8 PC2      SDA      TWI0 host SDA  (TWIROUTEA=ALT2)  ext 4.7k to VS
 *     9 PC3      SCL      TWI0 host SCL  (TWIROUTEA=ALT2)  ext 4.7k to VS
 *    10 PD0      VDDIO2   EA GPIO on the old VDDIO2 pad; SJ1 deleted 2026-07-30 (DNP before that), but C3 (100 nF -> GND, the DD-era decoupler) still hangs on the net -- no DC hold, so the internal pull-up (gpio_init) is still required; it just also charges C3 at boot
 *    11 PD1      STO_SNS    supercap-state sense  AIN1 (STO via R15/R16 divide-by-3)
 *    12 PD2      VSENSE   light sense (now SRC) + rail  AIN2 (ADC) + AINP0 (AC0+)
 *    18 VDD      VS       regulated 3.3 V LDO output (U9 TPS7A0233, STO->VS)
 *    19 GND      GND
 *    20 PF0      INT1     accel INT1 in  (PORTF pin interrupt)
 *    21 PF1      INT2     accel INT2 in  (PORTF pin interrupt)
 *    23 UPDI     UPDI     program (TC2030 pad TC1 / header J1)
 *    24 VDD      VS
 *    25 GND      GND
 *    EP          GND
 *
 * LED channel map (D1/D9/D10/D11 Schottkys removed in v4; only D2..D5 remain):
 *   D2->LDRV1->PA3/WO3 ; D3->LDRV2->PA2/WO2 ; D4->LDRV3->PA1/WO1 ; D5->LDRV4->PA0/WO0
 *   each LED: anode->ANODE common->SW2->STO (ON; bridge open = OFF) ; cathode->Kn->RN1 element->LDRV net->pin (see map above).
 *   RN1 is the 4x150R array that replaced discrete R1-R4 (2026-08-07): elements pair pins 1-8/2-7/3-6/4-5,
 *   wired so every K meets its documented LDRV -- the channel map above is unchanged.
 */
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#define F_CPU 1000000UL   /* OSCHF run frequency; see clocks_init in main.c */
#endif

/* ---- LEDs (low-side sink) on PORTA PA0..PA3 = TCA0 WO0..WO3 ----
 * TCA0 split: WO0..WO2 driven by LCMP0..2 (low timer), WO3 by HCMP0 (high timer).
 * PORTMUX.TCAROUTEA = PORTMUX_TCA0_PORTA_gc (0x00): WO0..WO3 land on PA0..PA3. */
#define LED_PORT        PORTA
#define LED_PA0_bm      PIN0_bm   /* LDRV4 / WO0 / LCMP0 */
#define LED_PA1_bm      PIN1_bm   /* LDRV3 / WO1 / LCMP1 */
#define LED_PA2_bm      PIN2_bm   /* LDRV2 / WO2 / LCMP2 */
#define LED_PA3_bm      PIN3_bm   /* LDRV1 / WO3 / HCMP0 */
#define LED_ALL_bm      (LED_PA0_bm | LED_PA1_bm | LED_PA2_bm | LED_PA3_bm)

/* ---- accel interrupt inputs on PORTF (no crystal -> PF0/PF1 are GPIO) ---- */
#define ACC_PORT        PORTF
#define ACC_INT1_bm     PIN0_bm   /* PF0 <- ADXL367 INT1 (tap, single+double) */
#define ACC_INT2_bm     PIN1_bm   /* PF1 <- ADXL367 INT2 (activity/motion)    */

/* ---- light/rail sense on PD2 ----
 * VSENSE = VIN/2 (R5/R6 = 1M each, C5 = 100nF). ADC sees ~VIN/2; x2 = VIN.
 * PD2 = AIN2 (ADC MUXPOS 0x02) and AINP0 (AC0 MUXPOS 0x00). */
#define VSENSE_AIN          ADC_MUXPOS_AIN2_gc        /* 0x02 */
#define VSENSE_DIVIDER      2                          /* VIN = VSENSE * 2   */

/* ---- STO sense-divider GATE on PC0 (net SNS_EN -> U10 TPS22916C ON) ----
 * 2026-08-09. R15/R16 used to hang permanently across STO: 3 M at the 4.65 V VOVCH ceiling
 * is 1.55 uA drawn from the TANK, every second of every day, awake or asleep -- larger than
 * any other single line in the standby ledger (accel 0.89, MCU+RTC 1.25, NFC FD 1.5) and
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 *
 * HIGH-side, deliberately. Gating the LOW leg with a GPIO looks cheaper and is wrong: with
 * the bottom open, C24 charges through R15 and STO_SNS floats to STO (4.65 V), which is
 * above VDD and forward-biases PD1's upper ESD clamp -- so it would still bleed ~0.4 uA AND
 * inject current into an ADC pin. Switching the top leaves R16 pulling STO_SNS to GND, so
 * the pin sits at 0 V and reads a clean, fail-safe zero when the gate is off.
 *
 * NO external pulldown is needed on SNS_EN (unlike R14 on U6/NFC_EN): the TPS22916 has a
 * SMART ON-pin pulldown -- 750 kOhm typ while ON <= VIL, automatically disconnected once ON
 * is driven high, so it costs nothing once enabled (datasheet SLVSDO5F, Features). That
 * holds the divider OFF while PC0 tristates during reset / UPDI / brown-out. */
#define SNS_EN_PORT         PORTC
#define SNS_EN_PIN_bm       PIN0_bm
/* Settle before converting: C24 (10 nF, shrunk from 100 nF for exactly this) through the
 * divider's 667k Thevenin = 6.68 ms tau NOMINAL. At 100 nF this would have been 335 ms and
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 * 53 ms awake on every poll of a slow cold start. The busy-wait is only cheap next to an
 * animation. */

/* ---- supercap-state sense on PD1 (AEM10300 STO via divide-by-3) ----
 * VS is now the regulated 3.3 V LDO output (constant), so the old VDD/10 read no longer tracks
 * the pack. STO (0.2..4.65 V) is divided by 3 into AIN1/PD1; the re-pointed sense_vdd_mv() reads
 * this channel and scales back: STO_mv = pin_mv * STO_DIVIDER. */
#define STO_SNS_AIN     ADC_MUXPOS_AIN1_gc     /* PD1 = AIN1 */
#define STO_DIVIDER     3                       /* R15 / R16 = 2 M / 1 M */

/* ---- AEM10300 charge-disable via Q2 buffer, gate on PA4 (net CHG_DIS_G), ACTIVE-HIGH ----
 * Since the 2026-07-23 cold-start-deadlock fix, PA4 drives the GATE of Q2 (BSS138LT1G
 * low-side buffer -- "2N7002" here until 2026-08-01; the BOM master and board fit the
 * BSS138, an equivalent logic-level NFET, and this file claims to be the as-built map)
 * -- not the AEM pin directly. Gate HIGH = Q2 on = EN_STO_CH pulled to GND = charging
 * DISABLED (quiets the >=10 MHz DCDC for an NFC read); gate LOW = Q2 off = EN_STO_CH floats to
 * its internal pull-up + R17/VINT = charging ENABLED. R18 (1 M gate pulldown) holds Q2 off --
 * charging ON -- whenever the MCU is dead/resetting/UPDI-parked, so a fully discharged card
 * always recharges (the old direct open-drain drive let the dead MCU's pin clamp hold the AEM's
 * enable low forever; see the design-notes second-sift addendum). PA4 is push-pull now and never
 * touches the 2.75 V-max AEM pin. Toggled in the FD both-edge handler in main.c. */
#define ENSTOCH_PORT    PORTA
#define ENSTOCH_PIN_bm  PIN4_bm
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 *
 * POWER-GATED: the chip draws ~195 uA continuously from VCC (datasheet Table 42,
 * 3.3V idle) with NO sleep state -- the dominant idle drain on the supercaps. A
 * high-side load switch now gates its VCC; enable is NFC_EN (PA7, active-HIGH),
 * default LOW = VCC off (~0 draw). Raise HIGH only while the MCU needs the I2C
 * side (provisioning / read / write), then drop it LOW again. NFC_EN gates ONLY
 * the MCU<->tag I2C path: a phone reading the static vCard, and the FD field-
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
/* NFC_EN: high-side load-switch enable for the NT3H2211 VCC. ACTIVE-HIGH.
 *   1 = NFC powered (I2C reachable).   0 = VCC off (default; ~0 draw). */
#define NFC_EN_PORT     PORTA
#define NFC_EN_PIN_bm   PIN7_bm

/* FD (field detect, U5 pin4) -> PA6, open-drain; the internal PA6 pull-up holds it (no external FD pull-up fitted).
 * FD-WAKE: a phone's field pulls FD low (FD_ON=00b, field-present = the POR
 * default). Per datasheet 8.4 the FD pin runs on the phone's field power, so it
 * works even with the tag's VCC gated off -- that is why FD-wake survives the
 * power-gate. main.c senses PA6 on BOTH edges: the falling edge (field arrives)
 * wakes the core to blank the LEDs for the read, and the rising edge (field leaves)
 * fires the acknowledge glow (see NFC_BLANK_ON_FIELD below). No I2C setup is needed
 * -- the field-present default does it. Firmware enables PA6's
 * internal pull-up, the SOLE FD pull-up (no external FD resistor in the design).
 * STANDING COST, corrected 2026-08-01 (pressure test; "only sinks current while FD
 * is held low" was wrong): the tag's own FD pin specs IL leakage 1.5 uA typ /
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#define USE_SUN_SWEEP   1

/* SWEEP_SUN_VIN_MV -- the in-sun trigger: VIN (the raw SRC solar node, no blocking
 * diode in v4; = VSENSE pin x2) at/above which we call it "strong sun." This is the
 * number the PCB side owed firmware; derived here, bench-tunable (it sets feel, not
 * safety -- SWEEP_CAPS_FULL_MV below is the hard gate).
 *
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 * So while CHARGING, SRC = 0.70 x Voc. Reaching 3600 mV would need Voc >= 5143 mV,
 * above the SM141K06TF's 4.15 V Voc -- so in ordinary charging this threshold is
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
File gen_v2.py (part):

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# Rationale: both decoupling caps sit awkwardly far from their pins AND choke the
# pin8/9/10 escape band. Moving them south/east opens the band and shortens decoupling.
NUDGE = {
    # C1 reverted to KiCad position (9.5,45.5): LDRV1 left the front, freeing the escape band; closer to VS pins = better decoupling.
    "C3": (7.5, 3.0),    # VDDIO2 decoupling: (4.0,45.5) -> (11.5,48.5), next to SJ1.2; kills the long west run. KEEP (load-bearing for VDDIO2 route).
}

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_DEL_SW={"SW1"}                                                      # snap-dome button removed; accel tap is the actuator now
for _k in [kk for kk in list(CUSTOM) if kk[0] in _DEL_SW]: CUSTOM.pop(_k,None)
abs_pads=[r for r in abs_pads if r[0] not in _DEL_SW]
_renet={("U1","21"):"INT1", ("U1","20"):"INT2",                     # commit PF1->INT1, PF0->INT2 (QFN NE corner, faces accel)
        ("U1","5"):"VSENSE", ("U1","3"):"BTN"}                       # move VSENSE to PC3 (pad5) = AIN31 (ADC) + AINP4 (AC) -> comparator wake-on-light on the clean W edge; BTN reserve -> PC1 (pad3). NOTE: PC3 is MVIO/PORTC -> disable MVIO fuse (VDDIO2 already tied to VS) for the analog functions.
abs_pads=[(r[0],r[1],_renet.get((r[0],r[1]),r[2]),*r[3:]) for r in abs_pads]
_ANODES={("D2","A"),("D3","A"),("D4","A"),("D5","A")}
abs_pads=[(r[0],r[1],"ANODE",*r[3:]) if (r[0],r[1]) in _ANODES else r for r in abs_pads]   # anodes now switch through SW2
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_clamp=[                                                                   # ref, pn, net, x, y, w, h   (all B-side)
  # PNP Q1 = WDFN 2x2 (BCP5316MTWG, case 515AA): 1=Base->CLBASE 2=Emitter->VIN 3+EP=Collector->GND
  ("Q1","1","CLBASE",41.5,48.5,0.40,0.50),("Q1","2","VS",41.5,49.5,0.40,0.50),("Q1","3","GND",40.3,49.0,1.00,1.40),
  # TLV431 DBZ/SOT-23-3 (TI Table 4-1): pin1=REF, pin2=CATHODE, pin3=ANODE.  K(2)=CLBASE  A(3)=GND  ref(1)=CLREF
  ("U4","1","CLREF",42.6,48.5,0.50,0.60),("U4","2","CLBASE",42.6,49.5,0.50,0.60),("U4","3","GND",43.8,49.0,0.50,0.60),
  ("R9","1","VS",40.5,45.15,1.20,1.00),("R9","2","CLBASE",40.5,47.05,1.20,1.00),                                 # base pull-up / cathode path ~1k (vert, N of cluster)
  ("R7","1","VS",45.5,47.05,1.20,1.00),("R7","2","CLREF",45.5,48.95,1.20,1.00),                                 # divider top 20k (horiz, E of U4)
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
# ---- button (SW1) + its D8 ESD TVS REMOVED -----------------------------------------------------
# Actuation is now the accelerometer (tap / double-tap -> INT -> wake -> glow burst); a tap is
# vibration so the Ti back-plate transmits it. BTN (PA7) is reserved out to the front middle-third
# for a possible future physical button (see the BTN reserve routing below).
# ---- second solar panel PV2 (mirror of PV1, bottom third, FRONT), wired PARALLEL with PV1 --------
# Doubles harvest so the card charges in dim/indoor light. Same nets as PV1 (VIN/GND), tied at VIN
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for ref,pn,net,x,y,w,h,sh,rt,side in abs_pads:
    if net not in ("GND","VS"): continue
    if ref.startswith("MH"): continue
    if ref=="U1": continue                     # U1 EP/pins handled manually (EP stitch + escape vias); skip auto-via on LDRV1's descent
    if in_void(x,y): continue
    if min(w,h)<0.55: continue                 # too small to drop a via in (QFN pins) -> route later
    key=(round(x,2),round(y,2))
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 ("GND","B",[P("U1","25"),(9.5,40.05)],TWN),     # bottom-edge GND pin -> up into EP
 ("VS","B",[P("U1","18"),(12.2,40.9),(13.0,43.0)],TWN),  # right-edge VS pin -> B due-E at y40.9 (clears pin17 NC) -> SE to escape via (clear of SCL F corridor)
 ("VS","B",[P("U1","24"),(9.9,38.3)],TWN),       # bottom-edge VS pin -> fine escape via -> In2
 # ---- MID bus: 4 supercap mid taps (SC1.N/SC2.P top, SC3.N/SC4.P bottom) + 3 U2 balancer pins. Open-area routing, skirting RIGHT of the glow window. ----
 # ---- MID balance bus: moved to In2 (back-side cleanup). 6 surfacing vias; SC1.N/SC2.P land @y26 (UNDER panel -> hidden), U2.4/U2.6 fine via-in-pad, SC3.N/SC4.P @y57.5. U2.6-U2.7 stay bridged on B so one via serves the pair. ----
 ("MID","In2",[(15.5,26.0),(35.3,26.0)],TW),                                         # top pair bus on In2 (y26 = under panel, both vias hidden)
 ("MID","In2",[(35.3,26.0),(38.5,26.0),(38.5,41.8),P("U2","4")],TW),                 # down right margin (E of glow window) -> U2.4 via
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 ("LDRV1","B",[P("U1","26"),(9.3,37.6)],TWN),                                        # dog-bone NE -> outer-row fine via
 ("LDRV1","In2",[(9.3,37.6),(9.3,50.3),(16.6,50.3),P("R1","2")],TW),                 # In2: descend x9.3 -> N-corridor y50.3 -> up onto R1.2 (via-in-pad) [F-free]
 # ---- LDRV2/3/4: reversal handled by descend->parallel-lane->rise topology (no crossing). Descents on inner layers clear the B-side caps' pads; only via rings to dodge. ----
 ("LDRV2","B",[P("U1","27"),(8.7,38.0)],TWN),                                        # pin27 dog-bone N -> fine escape via
 ("LDRV2","In3",[(8.7,38.0),(9.3,39.0),(9.3,50.5),(22.91,50.5),P("R2","2")],TW),     # In3: thread EP gap x9.3, N-corridor y50.5 (N of SB bridges), up onto R2.2 (via-in-pad)
 ("LDRV3","B",[P("U1","28"),(8.0,37.7)],TWN),                                        # pin28 dog-bone N -> fine escape via (staggered N of LDRV2)
 ("LDRV3","In2",[(8.0,37.7),(7.9,39.0),(7.9,50.95),(29.2,50.95),P("R3","2")],TW),    # In2: descend W of EP, N-corridor y50.95 (clears C5.2 GND via + SB), up onto R3.2
 ("LDRV4","B",[P("U1","1"),(6.8,39.3)],TWN),                                         # left-edge pin1 -> fine escape via (W)
 ("LDRV4","In3",[(6.8,39.3),(7.9,41.2),(7.9,51.25),(35.2,51.25),P("R4","2")],TW),    # In3: W descent, N-corridor y51.25 (N of SB), up onto R4.2
 # ---- SB1-4 disable jumpers: each ballast (LDRVn) also feeds SBn.1; SBn.2 is GND. Short B stub ballast -> bridge pad. ----
 ("LDRV1","B",[P("R1","2"),P("SB1","1")],TW),
 ("LDRV2","B",[P("R2","2"),P("SB2","1")],TW),
 ("LDRV3","B",[P("R3","2"),P("SB3","1")],TW),
 ("LDRV4","B",[P("R4","2"),P("SB4","1")],TW),
 # ---- VSENSE: now on PC3 (pad5, W edge) = AIN31+AINP4 -> B escape W (crosses BTN's In2 descent on a different layer) -> In2 x5.5 descent to divider node R6.1; node tied R5.2 + C5.1 ----
 ("VSENSE","B",[P("U1","5"),(6.8,41.3)],TWN),                                        # pad5 (PC3) short B escape -> via right at the pad (keeps the all-layer via clear of J1.3's B pad)
 ("VSENSE","In2",[(6.8,41.3),(5.5,42.0),(5.5,50.4)],TW),                             # In2 trace W to x5.5 (J1.3 is B-only, no In2 conflict) -> descend to R5.2 node
 ("VSENSE","B",[P("R6","1"),P("R5","2")],TWN),                                       # R6.1 - R5.2 (adjacent VSENSE pads)
 ("VSENSE","B",[P("R6","1"),(6.65,51.4),(6.45,51.4),P("C5","1")],TWN),               # R6.1 -> C5.1 (S to the relocated filter cap)
 # ---- PC0: pin6 -> In3 W-zone descent (between R5.2/R6.1) -> JP2.2 ----
 ("PC0","B",[P("U1","6"),(7.0,41.7),(5.0,42.4)],TWN),                                           # pin6 escape W -> fine via
 ("PC0","In3",[(5.0,42.4),(4.9,43.5),(4.9,54.0),P("JP2","2")],TW),                   # In3 W-zone -> divider gap -> JP2.2
 # ---- PC1: pin7 -> In2 middle-zone descent (between R6.2/C5.2 GND) -> JP2.3 ----
 ("PC1","B",[P("U1","7"),(7.3,42.8)],TWN),                                           # pin7 escape W -> fine via
 ("PC1","In2",[(7.3,42.8),(7.4,44.5),(7.4,52.5),(6.63,53.8),P("JP2","3")],TW),       # In2 mid-zone -> below divider -> JP2.3
 # UPDI: fine via -> F T-junction (north to TC1.1, west to J1.1)
 ("UPDI","B",[P("U1","23"),(10.5,37.6)],TWN),                                        # dog-bone NE -> outer-row fine via
 ("UPDI","In3",[(10.5,37.6),(11.5,37.0),(11.5,26.0),(13.3,24.0),(13.3,15.63),(12.665,15.63)],TW),  # In3: x11.5 down past JP1, jog E below it, thread between the upper align holes @x13.3, W into shifted TC1.1
 ("UPDI","In3",[(10.5,37.6),(9.0,36.0),(4.7,36.0)],TW),                              # In3 west (N of C2 VS via) to J1 column [F-free]
 ("UPDI","B",[(4.7,36.0),P("J1","1")],TW),                                           # via drop -> J1.1
 # ---- SDA: route like SCL/VDDIO2 - stay on B under LDRV1/2/3's F descents (free, diff layer), then pop to F for the north-run. No escape/dip vias to crowd the SW corridor. ----
 ("SDA","B",[P("U1","8"),(8.3,44.5),(12.0,44.5)],TWN),                               # B: S off pin8 -> E under LDRV1/2/3 F descents -> F-transition
 ("SDA","In3",[(12.0,44.5),(12.0,33.0),P("JP1","1")],TW),                            # In3 up x12 (W of GND/SCL vias), short jog to relocated JP1.1
 # ---- SCL: pin9 (B) runs on B under LDRV1's F descent AND SDA's F north-run (both free, diff layer), then pops to F for a clean north-run up the corridor -> JP1.2 ----
 ("SCL","B",[P("U1","9"),(8.7,44.0),(12.5,44.0)],TWN),                               # B: S off pin9 -> E under LDRV1(F) + SDA(F) -> F-transition
 ("SCL","In2",[(12.5,44.0),(12.3,43.0),(12.3,35.5),P("JP1","2")],TW),                            # In2 up x12.3, short jog to relocated JP1.2
 # ---- VDDIO2: pin10 (B) diagonals E of LDRV1 (S of SCL's deeper run, so no cross), E to SJ1.2; C3 (nudged next to SJ1.2) chains off SJ1.2 ----
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

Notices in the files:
PCB/README.md:
Part of SOLAR-GLOW · DRH. © 2026 Devin R. Horowitz. MIT License (see `../LICENSE`).
README.md:
© 2026 Devin R. Horowitz. Released under the [MIT License](LICENSE).
